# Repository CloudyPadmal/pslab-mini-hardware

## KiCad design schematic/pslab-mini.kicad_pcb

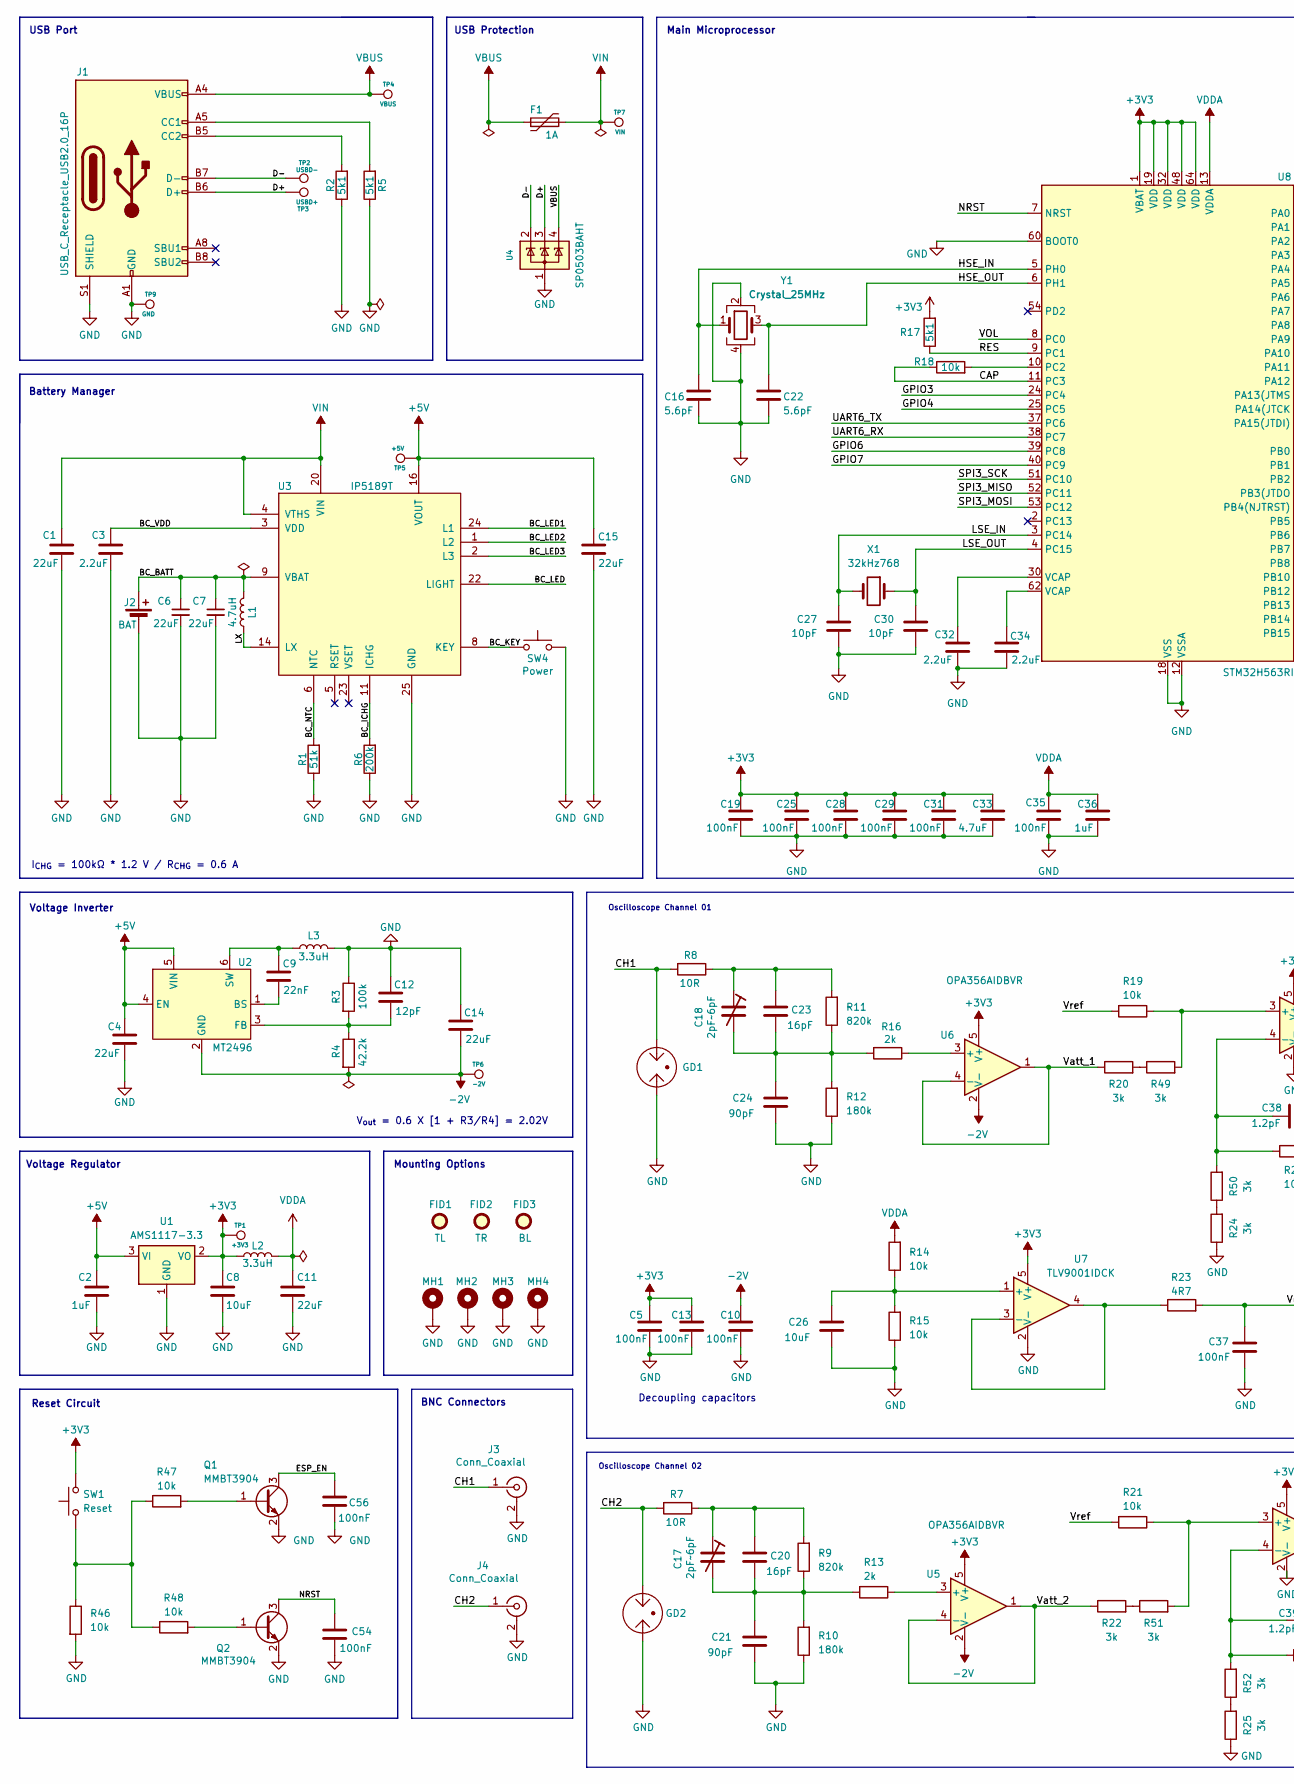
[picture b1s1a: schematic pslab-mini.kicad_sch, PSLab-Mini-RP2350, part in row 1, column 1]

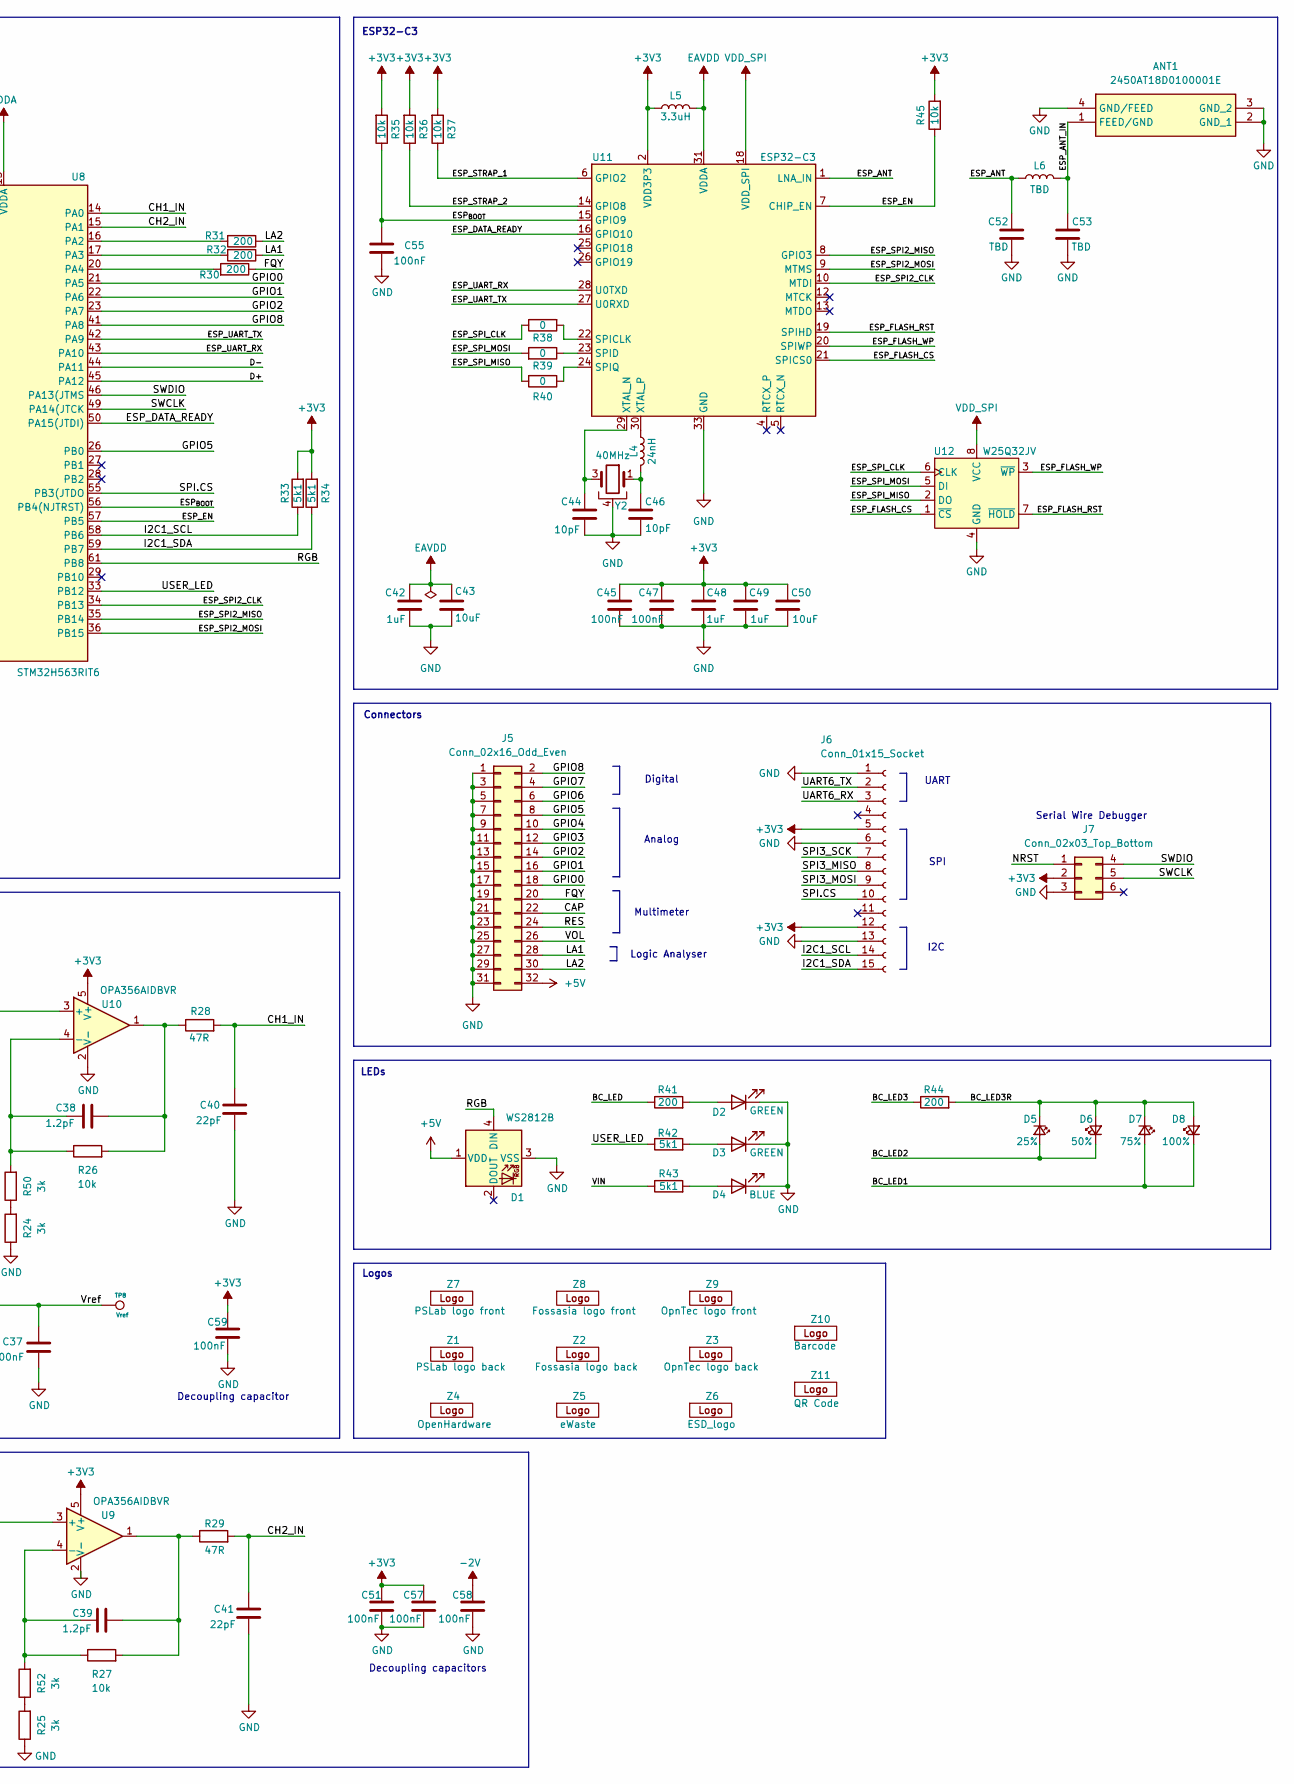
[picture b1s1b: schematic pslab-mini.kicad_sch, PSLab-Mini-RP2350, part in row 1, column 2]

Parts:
ANT1: 2450AT18D0100001E; Mouser Part Number 609-2450AT18D0100001
C1, C4, C6, C7, C11, C14, C15: 22uF; C_0805_2012Metric; Part Number (LCSC) C602037
C2, C36, C42, C48, C49: 1uF; C_0603_1608Metric; Part Number (LCSC) C15849
C3, C32, C34: 2.2uF; C_0805_2012Metric; Part Number (LCSC) C19110
C5, C10, C13, C51, C57, C58, C59: 100nF; C_0402_1005Metric; Part Number (LCSC) C1525
C8, C26, C43, C50: 10uF; C_0805_2012Metric; Part Number (LCSC) C1713
C9: 22nF; C_0603_1608Metric; Part Number (LCSC) C21122
C12: 12pF; C_0603_1608Metric; Part Number (LCSC) C107034
C16, C22: 5.6pF; C_0603_1608Metric; Part Number (LCSC) C309464
C17, C18: 2pF~6pF; STC3MA06-T1; Part Number (LCSC) C22468120
C19, C25, C28, C29, C31, C35, C37, C45, C47, C54, C55, C56: 100nF; C_0603_1608Metric; Part Number (LCSC) C14663
C20, C23: 16pF; C_0603_1608Metric; Part Number (LCSC) C327125
C21, C24: 90pF; C_0603_1608Metric; Part Number (LCSC) C501849
C27, C30, C44, C46: 10pF; C_0603_1608Metric; Part Number (LCSC) C1634
C33: 4.7uF; C_0805_2012Metric; Part Number (LCSC) C98192
C38, C39: 1.2pF; C_0603_1608Metric; Part Number (LCSC) C519098
C40, C41: 22pF; C_0603_1608Metric; Part Number (LCSC) C1653
C52, C53: TBD; C_0402_1005Metric; Part Number (LCSC) C72134
D1: WS2812B; LED_WS2812B_PLCC4_5.0x5.0mm_P3.2mm; Part Number (LCSC) C114586
D2, D3: GREEN; LED_0805_2012Metric; Part Number (LCSC) C965815
D4: BLUE; LED_0805_2012Metric; Part Number (LCSC) C965817
D5: 25%; LED_0603_1608Metric; Part Number (LCSC) C965808
D6: 50%; LED_0603_1608Metric; Part Number (LCSC) C965808
D7: 75%; LED_0603_1608Metric; Part Number (LCSC) C965808
D8: 100%; LED_0603_1608Metric; Part Number (LCSC) C965808
F1: 1A; Fuse_1206_3216Metric; Part Number (LCSC) C22435907
FID1: TL; Fiducial_0.5mm_Mask1.5mm
FID2: TR; Fiducial_0.5mm_Mask1.5mm
FID3: BL; Fiducial_0.5mm_Mask1.5mm
GD1, GD2: SMD3216-090N; Part Number (LCSC) C22439020
J1: USB_C_Receptacle_USB2.0_16P; USB_C_Receptacle_G-Switch_GT-USB-7010ASV; MPN GT-USB-7010ASV; LCSC# C2988369
J2: BAT; 2.0mm_connector_edge; Part Number (LCSC) C295747
J3, J4: Conn_Coaxial; BNC_connector_dosinconn DOSIN-801-0050; Part Number (LCSC) C521210
J5: Conn_02x16_Odd_Even; PinSocket_2x16_P2.54mm_Vertical; Part Number (LCSC) C2883989
J6: Conn_01x15_Socket; PinSocket_1x15_P2.54mm_Vertical; Part Number (LCSC) C2932676
J7: Conn_02x03_Top_Bottom; pslab-mini_2x03_P2.54mm
L1: 4.7uH; L_0805_2012Metric; Part Number (LCSC) C131082
L2, L3, L5: 3.3uH; L_0603_1608Metric; Part Number (LCSC) C162581
L4: 24nH; L_0402_1005Metric; Part Number (LCSC) C167472
L6: TBD; L_0402_1005Metric; Part Number (LCSC) C77108
MH1, MH2, MH3, MH4: MountingHole_Pad; MountingHole_2.75mm_Pad
Q1, Q2: MMBT3904; SOT-416; Part Number (LCSC) C242260
R1: 51k; R_0603_1608Metric; MPN RC0603FR-0751KL; LCSC# C107231
R2, R5, R17, R33, R34, R42, R43: 5k1; R_0603_1608Metric; Part Number (LCSC) C105580
R3: 100k; R_0603_1608Metric; Part Number (LCSC) C14675
R4: 42.2k; R_0603_1608Metric; Part Number (LCSC) C273741
R6: 200k; R_0603_1608Metric; MPN RC0603FR-07200KL; LCSC# C105574
R7, R8: 10R; R_0603_1608Metric; Part Number (LCSC) C109318
R9, R11: 820k; R_0603_1608Metric; Part Number (LCSC) C861571
R10, R12: 180k; R_0603_1608Metric; Part Number (LCSC) C326731
R13, R16: 2k; R_0603_1608Metric; Part Number (LCSC) C105576
R14, R15, R19, R21, R26, R27: 10k; R_0603_1608Metric; Part Number (LCSC) C95204
R18, R35, R36, R37, R45, R46, R47, R48: 10k; R_0603_1608Metric; Part Number (LCSC) C98220
R20, R22, R24, R25, R49, R50, R51, R52: 3k; R_0402_1005Metric; Part Number (LCSC) C281777
R23: 4R7; R_0603_1608Metric; Part Number (LCSC) C326830
R28, R29: 47R; R_0603_1608Metric; Part Number (LCSC) C114623
R30, R31, R32: 200; R_0603_1608Metric; Part Number (LCSC) C114664
R38, R39, R40: 0; R_0402_1005Metric; Part Number (LCSC) C106231
R41, R44: 200; R_0402_1005Metric; Part Number (LCSC) C114764
SW1: Reset; SW_Tactile_SPST_NO_Straight_CK_PTS636Sx25SMTRLFS; Part Number (LCSC) C2689642
SW4: Power; SW_Tactile_SPST_NO_Straight_CK_PTS636Sx25SMTRLFS; Part Number (LCSC) C2689642
TP1: +3V3; Test_Point_0.8mm
TP2: USBD-; TestPoint_Pad_1.0x1.0mm
TP3: USBD+; TestPoint_Pad_1.0x1.0mm
TP4: VBUS; TestPoint_Pad_1.0x1.0mm
TP5: +5V; Test_Point_0.8mm
TP6: -2V; Test_Point_0.8mm
TP7: VIN; Test_Point_0.8mm
TP8: Vref; Test_Point_0.8mm
TP9: GND; TestPoint_Pad_1.0x1.0mm
U1: AMS1117-3.3; SOT-223-3_TabPin2; Part Number (LCSC) C6186; LCSC# C6186
U2: MT2496; SOT-23-6; Part Number (LCSC) C384594; LCSC# C384594
U3: IP5189T; QFN-24-1EP_4x4mm_P0.5mm_EP2.6x2.6mm; MPN IP5189T-QW; LCSC# C605436
U4: SP0503BAHT; SOT-143; Part Number (LCSC) C7074
U5, U6, U9, U10: OPA356AIDBVR; SOT-23-5; Part Number (LCSC) C183100
U7: TLV9001IDCK; SOT-353_SC-70-5; Part Number (LCSC) C398362
U8: STM32H563RIT6; LQFP-64_10x10mm_P0.5mm; Part Number (LCSC) C20619634
U11: ESP32-C3; QFN-32-1EP_5x5mm_P0.5mm_EP3.7x3.7mm; Part Number (LCSC) C2838500; LCSC# C2838500
U12: W25Q32JV; SOIC-8_5.3x5.3mm_P1.27mm; MPN W25Q32JVSSIQ; LCSC# C179173
X1: 32kHz768; Crystal_SMD_3215-2Pin_3.2x1.5mm; Part Number (LCSC) C32346
Y1: Crystal_25MHz; Crystal_SMD_3225-4Pin_3.2x2.5mm; Part Number (LCSC) C9006
Y2: 40MHz; Crystal_SMD_3225-4Pin_3.2x2.5mm; Part Number (LCSC) C5261245
Z1: PSLab logo back; logo_pslab.io
Z2: Fossasia logo back; logo_fossasia
Z3: OpnTec logo back; logo_opntec
Z4: OpenHardware; logo_open_source_hardware
Z5: eWaste; logo_eWaste
Z6: ESD_logo; ESD-Logo_6.6x6mm_SilkScreen
Z7: PSLab logo front; logo_pslab.io
Z8: Fossasia logo front; logo_fossasia
Z9: OpnTec logo front; logo_opntec
Z10: Barcode
Z11: QR Code; Website_QR

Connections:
+3V3: C5.1, C8.2, C13.1, C19.1, C25.1, C28.1, C29.1, C31.1, C33.1, C45.1, C47.1, C48.1, C49.1, C50.1, C51.1, C57.1, C59.1, J6.5, J6.12, J7.2, L2.2, L5.1, R17.2, R33.2, R34.2, R35.2, R36.2, R37.2, R45.2, SW1.2, TP1.1, U1.2 (VO), U5.5 (V+), U6.5 (V+), U7.5 (V+), U8.1 (VBAT), U8.19 (VDD), U8.32 (VDD), U8.48 (VDD), U8.64 (VDD), U9.5 (V+), U10.5 (V+), U11.2 (VDD3P3), U11.3 (VDD3P3), U11.11 (VDD3P3_RTC), U11.17 (VDD3P3_CPU)
+5V: C2.2, C4.1, C15.1, D1.1 (VDD), J5.32, TP5.1, U1.3 (VI), U2.4 (EN), U2.5 (VIN), U3.16 (VOUT), U3.17 (VOUT)
-2V: C10.1, C14.2, C58.1, R4.2, TP6.1, U2.2 (GND), U5.2 (V-), U6.2 (V-)
/BC_BATT: C6.1, C7.1, J2.1 (+), L1.2, U3.9 (VBAT)
/BC_ICHG: R6.2, U3.11 (ICHG)
/BC_KEY: SW4.2, U3.8 (KEY)
/BC_LED: R41.1, U3.22 (LIGHT)
/BC_LED1: D7.2 (A), D8.1 (K), U3.24 (L1)
/BC_LED2: D5.2 (A), D6.1 (K), U3.1 (L2)
/BC_LED3: R44.1, U3.2 (L3)
/BC_LED3R: D5.1 (K), D6.2 (A), D7.1 (K), D8.2 (A), R44.2
/BC_NTC: R1.2, U3.6 (NTC)
/BC_VDD: C3.1, U3.3 (VDD)
/CAP: J5.22, R18.1, U8.11 (PC3)
/CH1: GD1.2, J3.1 (In), R8.2
/CH1_IN: C40.2, R28.2, U8.14 (PA0)
/CH2: GD2.2, J4.1 (In), R7.2
/CH2_IN: C41.2, R29.2, U8.15 (PA1)
/D+: J1.A6 (D+), J1.B6 (D+), TP3.1, U4.3 (K), U8.45 (PA12)
/D-: J1.A7 (D-), J1.B7 (D-), TP2.1, U4.2 (K), U8.44 (PA11)
/ESP_ANT: C52.2, L6.2, U11.1 (LNA_IN)
/ESP_ANT_IN: ANT1.1 (FEED/GND), C53.2, L6.1
/ESP_DATA_READY: U8.50 (PA15(JTDI)), U11.16 (GPIO10)
/ESP_EN: C56.2, Q1.3 (C), R45.1, U8.57 (PB5), U11.7 (CHIP_EN)
/ESP_FLASH_CS: U11.21 (SPICS0), U12.1 (~CS)
/ESP_FLASH_RST: U11.19 (SPIHD), U12.7 (~HOLD)
/ESP_FLASH_WP: U11.20 (SPIWP), U12.3 (~WP)
/ESP_SPI2_CLK: U8.34 (PB13), U11.10 (MTDI)
/ESP_SPI2_MISO: U8.35 (PB14), U11.8 (GPIO3)
/ESP_SPI2_MOSI: U8.36 (PB15), U11.9 (MTMS)
/ESP_SPI_CLK: R38.1, U12.6 (CLK)
/ESP_SPI_MISO: R40.2, U12.2 (DO)
/ESP_SPI_MOSI: R39.2, U12.5 (DI)
/ESP_STRAP_1: R37.1, U11.6 (GPIO2)
/ESP_STRAP_2: R36.1, U11.14 (GPIO8)
/ESP_UART_RX: U8.43 (PA10), U11.28 (U0TXD)
/ESP_UART_TX: U8.42 (PA9), U11.27 (U0RXD)
/ESP_{BOOT}: C55.2, R35.1, U8.56 (PB4(NJTRST)), U11.15 (GPIO9)
/FQY: J5.20, R30.1
/GPIO0: J5.18, U8.21 (PA5)
/GPIO1: J5.16, U8.22 (PA6)
/GPIO2: J5.14, U8.23 (PA7)
/GPIO3: J5.12, U8.24 (PC4)
/GPIO4: J5.10, U8.25 (PC5)
/GPIO5: J5.8, U8.26 (PB0)
/GPIO6: J5.6, U8.39 (PC8)
/GPIO7: J5.4, U8.40 (PC9)
/GPIO8: J5.2, U8.41 (PA8)
/HSE_IN: C16.1, U8.5 (PH0), Y1.1
/HSE_OUT: C22.1, U8.6 (PH1), Y1.3
/I2C1_SCL: J6.14, R33.1, U8.58 (PB6)
/I2C1_SDA: J6.15, R34.1, U8.59 (PB7)
/LA1: J5.28, R32.1
/LA2: J5.30, R31.1
/LSE_IN: C27.1, U8.3 (PC14), X1.2
/LSE_OUT: C30.1, U8.4 (PC15), X1.1
/LX: L1.1, U3.13 (LX), U3.14 (LX), U3.15 (LX)
/NRST: C54.1, J7.1, Q2.3 (C), U8.7 (NRST)
/RES: J5.24, R17.1, U8.9 (PC1)
/RGB: D1.4 (DIN), U8.61 (PB8)
/SPI3_MISO: J6.8, U8.52 (PC11)
/SPI3_MOSI: J6.9, U8.53 (PC12)
/SPI3_SCK: J6.7, U8.51 (PC10)
/SPI.CS: J6.10, U8.55 (PB3(JTDO)
/SWCLK: J7.5, U8.49 (PA14(JTCK)
/SWDIO: J7.4, U8.46 (PA13(JTMS)
/UART6_RX: J6.3, U8.38 (PC7)
/UART6_TX: J6.2, U8.37 (PC6)
/USER_LED: R42.1, U8.33 (PB12)
/VOL: J5.26, U8.8 (PC0)
/Vatt_1: R20.1, U6.1, U6.4 (-)
/Vatt_2: R22.1, U5.1, U5.4 (-)
/Vref: C37.1, R19.2, R21.2, R23.2, TP8.1
EAVDD: C42.1, C43.1, L5.2, U11.31 (VDDA), U11.32 (VDDA)
GND: ANT1.2 (GND_1), ANT1.3 (GND_2), ANT1.4 (GND/FEED), C1.2, C2.1, C3.2, C4.2, C5.2, C6.2, C7.2, C8.1, C10.2, C11.2, C12.1, C13.2, C14.1, C15.2, C16.2, C19.2, C21.2, C22.2, C24.2, C25.2, C26.2, C27.2, C28.2, C29.2, C30.2, C31.2, C32.2, C33.2, C34.2, C35.2, C36.2, C37.2, C40.1, C41.1, C42.2, C43.2, C44.1, C45.2, C46.1, C47.2, C48.2, C49.2, C50.2, C51.2, C52.1, C53.1, C54.2, C55.1, C56.1, C57.2, C58.2, C59.2, D1.3 (VSS), D2.1 (K), D3.1 (K), D4.1 (K), GD1.1, GD2.1, J1.A1 (GND), J1.A12 (GND), J1.B1 (GND), J1.B12 (GND), J1.S1 (SHIELD), J2.2 (-), J3.2 (Ext), J4.2 (Ext), J5.1, J5.3, J5.5, J5.7, J5.9, J5.11, J5.13, J5.15, J5.17, J5.19, J5.21, J5.23, J5.25, J5.27, J5.29, J5.31, J6.1, J6.6, J6.13, J7.3, L3.2, MH1.1, MH2.1, MH3.1, MH4.1, Q1.2 (E), Q2.2 (E), R1.1, R2.1, R3.1, R5.1, R6.1, R10.1, R12.1, R15.1, R24.1, R25.1, R46.2, SW4.1, TP9.1, U1.1 (GND), U3.7 (AGND), U3.12 (PGND), U3.25 (GND), U4.1 (A), U7.2 (V-), U8.12 (VSSA), U8.18 (VSS), U8.31 (VSS), U8.47 (VSS), U8.60 (BOOT0), U8.63 (VSS), U9.2 (V-), U10.2 (V-), U11.33 (GND), U12.4 (GND), Y1.2, Y1.4, Y2.2, Y2.4
unnamed: C17.1, C20.1, R7.1, R9.2
unnamed: C17.2, C20.2, C21.1, R9.1, R10.2, R13.2
unnamed: C18.1, C23.1, R8.1, R11.2
unnamed: C18.2, C23.2, C24.1, R11.1, R12.2, R16.2
unnamed: C32.1, U8.30 (VCAP)
unnamed: C34.1, U8.62 (VCAP)
unnamed: C38.2, R26.2, R28.1, U10.1
unnamed: C39.2, R27.2, R29.1, U9.1
unnamed: C46.2, L4.1, Y2.1
unnamed: D2.2 (A), R41.2
unnamed: D3.2 (A), R42.2
unnamed: D4.2 (A), R43.2
unnamed: J1.A5 (CC1), R5.2
unnamed: J1.B5 (CC2), R2.2
unnamed: Q1.1 (B), R47.2
unnamed: Q2.1 (B), R48.2
unnamed: R20.2, R49.1
unnamed: R22.2, R51.1
unnamed: R24.2, R50.1
unnamed: R25.2, R52.1
unnamed: R46.1, R47.1, R48.1, SW1.1
unnamed: C9.2, U2.1 (BS)
unnamed: C12.2, R3.2, R4.1, U2.3 (FB)
unnamed: C9.1, L3.1, U2.6 (SW)
unnamed: R13.1, U5.3 (+)
unnamed: R16.1, U6.3 (+)
unnamed: C26.1, R14.1, R15.2, U7.1 (+)
unnamed: R23.1, U7.3 (-), U7.4
unnamed: R31.2, U8.16 (PA2)
unnamed: R32.2, U8.17 (PA3)
unnamed: R30.2, U8.20 (PA4)
unnamed: R18.2, U8.10 (PC2)
unnamed: R21.1, R51.2, U9.3 (+)
unnamed: C39.1, R27.1, R52.2, U9.4 (-)
unnamed: R19.1, R49.2, U10.3 (+)
unnamed: C38.1, R26.1, R50.2, U10.4 (-)
unnamed: R38.2, U11.22 (SPICLK)
unnamed: R39.1, U11.23 (SPID)
unnamed: R40.1, U11.24 (SPIQ)
unnamed: C44.2, U11.29 (XTAL_N), Y2.3
unnamed: L4.2, U11.30 (XTAL_P)
VBUS: F1.1, J1.A4 (VBUS), J1.A9 (VBUS), J1.B4 (VBUS), J1.B9 (VBUS), TP4.1, U4.4 (K)
VDDA: C11.1, C35.1, C36.1, L2.1, R14.2, U8.13 (VDDA)
VDD_SPI: U11.18 (VDD_SPI), U12.8 (VCC)
VIN: C1.1, F1.2, R43.1, TP7.1, U3.4 (VTHS), U3.20 (VIN), U3.21 (VIN)

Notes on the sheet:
Voltage Regulator
Battery Manager
Logos
I2C
Connectors
SPI
I_{CHG} = 100kΩ * 1.2 V / R_{CHG} = 0.6 A
Oscilloscope Channel 01
UART
Multimeter
Analog
Voltage Inverter
Reset Circuit
BNC Connectors
Serial Wire Debugger
Decoupling capacitors
USB Protection
V_{out} = 0.6 X [1 + R3/R4] = 2.02V
Main Microprocessor
Logic Analyser
LEDs
Decoupling capacitor
Mounting Options
USB Port
Digital
ESP32-C3
Oscilloscope Channel 02

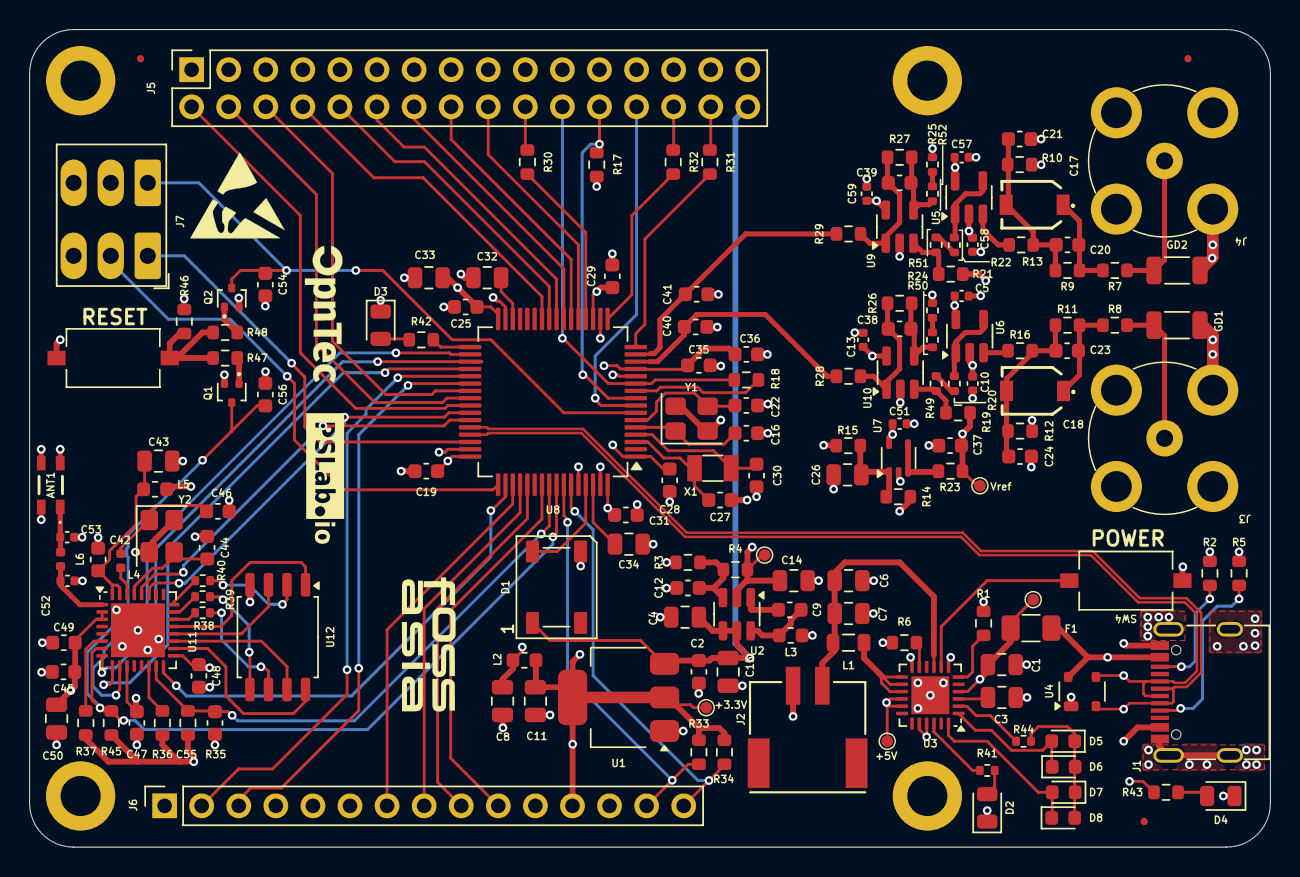
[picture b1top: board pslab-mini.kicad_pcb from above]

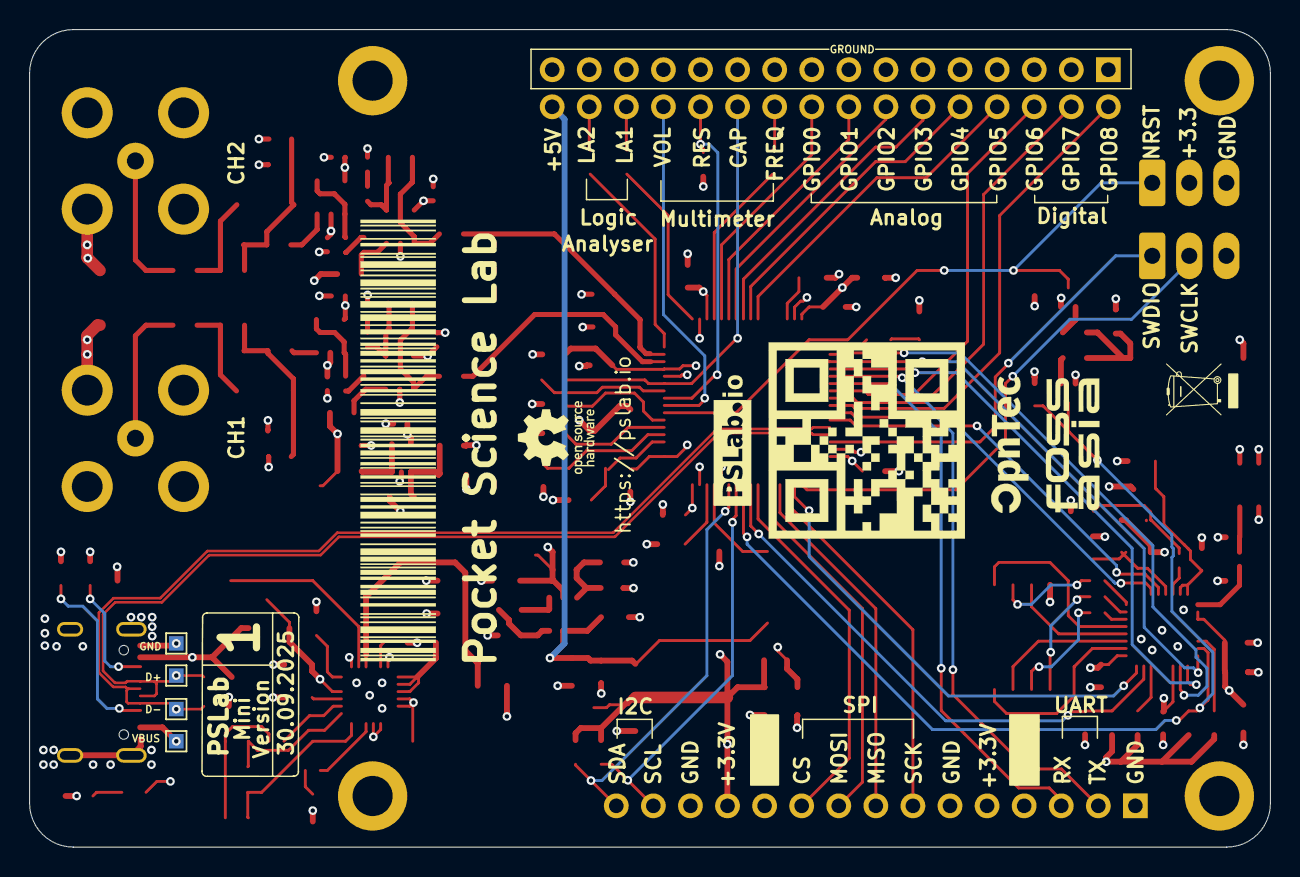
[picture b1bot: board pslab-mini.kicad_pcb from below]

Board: 4 copper layers, 85.0 x 56.0 mm, 182 parts (11 on the bottom side), 120 nets.

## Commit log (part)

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2025-07-28 chore: PR comment with latest schematic
2025-07-30 token based PR comments
2025-07-30 parent triggers
2025-07-30 chore: PAT-based PR comments
2025-08-11 chore: previews for both layouts and schematics
2025-08-12 namings
2025-08-12 artifacts
2025-08-12 tables
2025-08-13 chore: fix path mismatch
2025-08-13 renaming
2025-08-13 Cleanup layout previews
2025-08-15 chore: no build previews if no changes are detected
2025-08-15 schematic previews for PR15:32c3146
2025-08-24 Cleanup schematic previews
2026-02-08 update CH1 and CH2 (#62)
